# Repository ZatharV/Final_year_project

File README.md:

# Final_year_project

Industrial IoT 4.0

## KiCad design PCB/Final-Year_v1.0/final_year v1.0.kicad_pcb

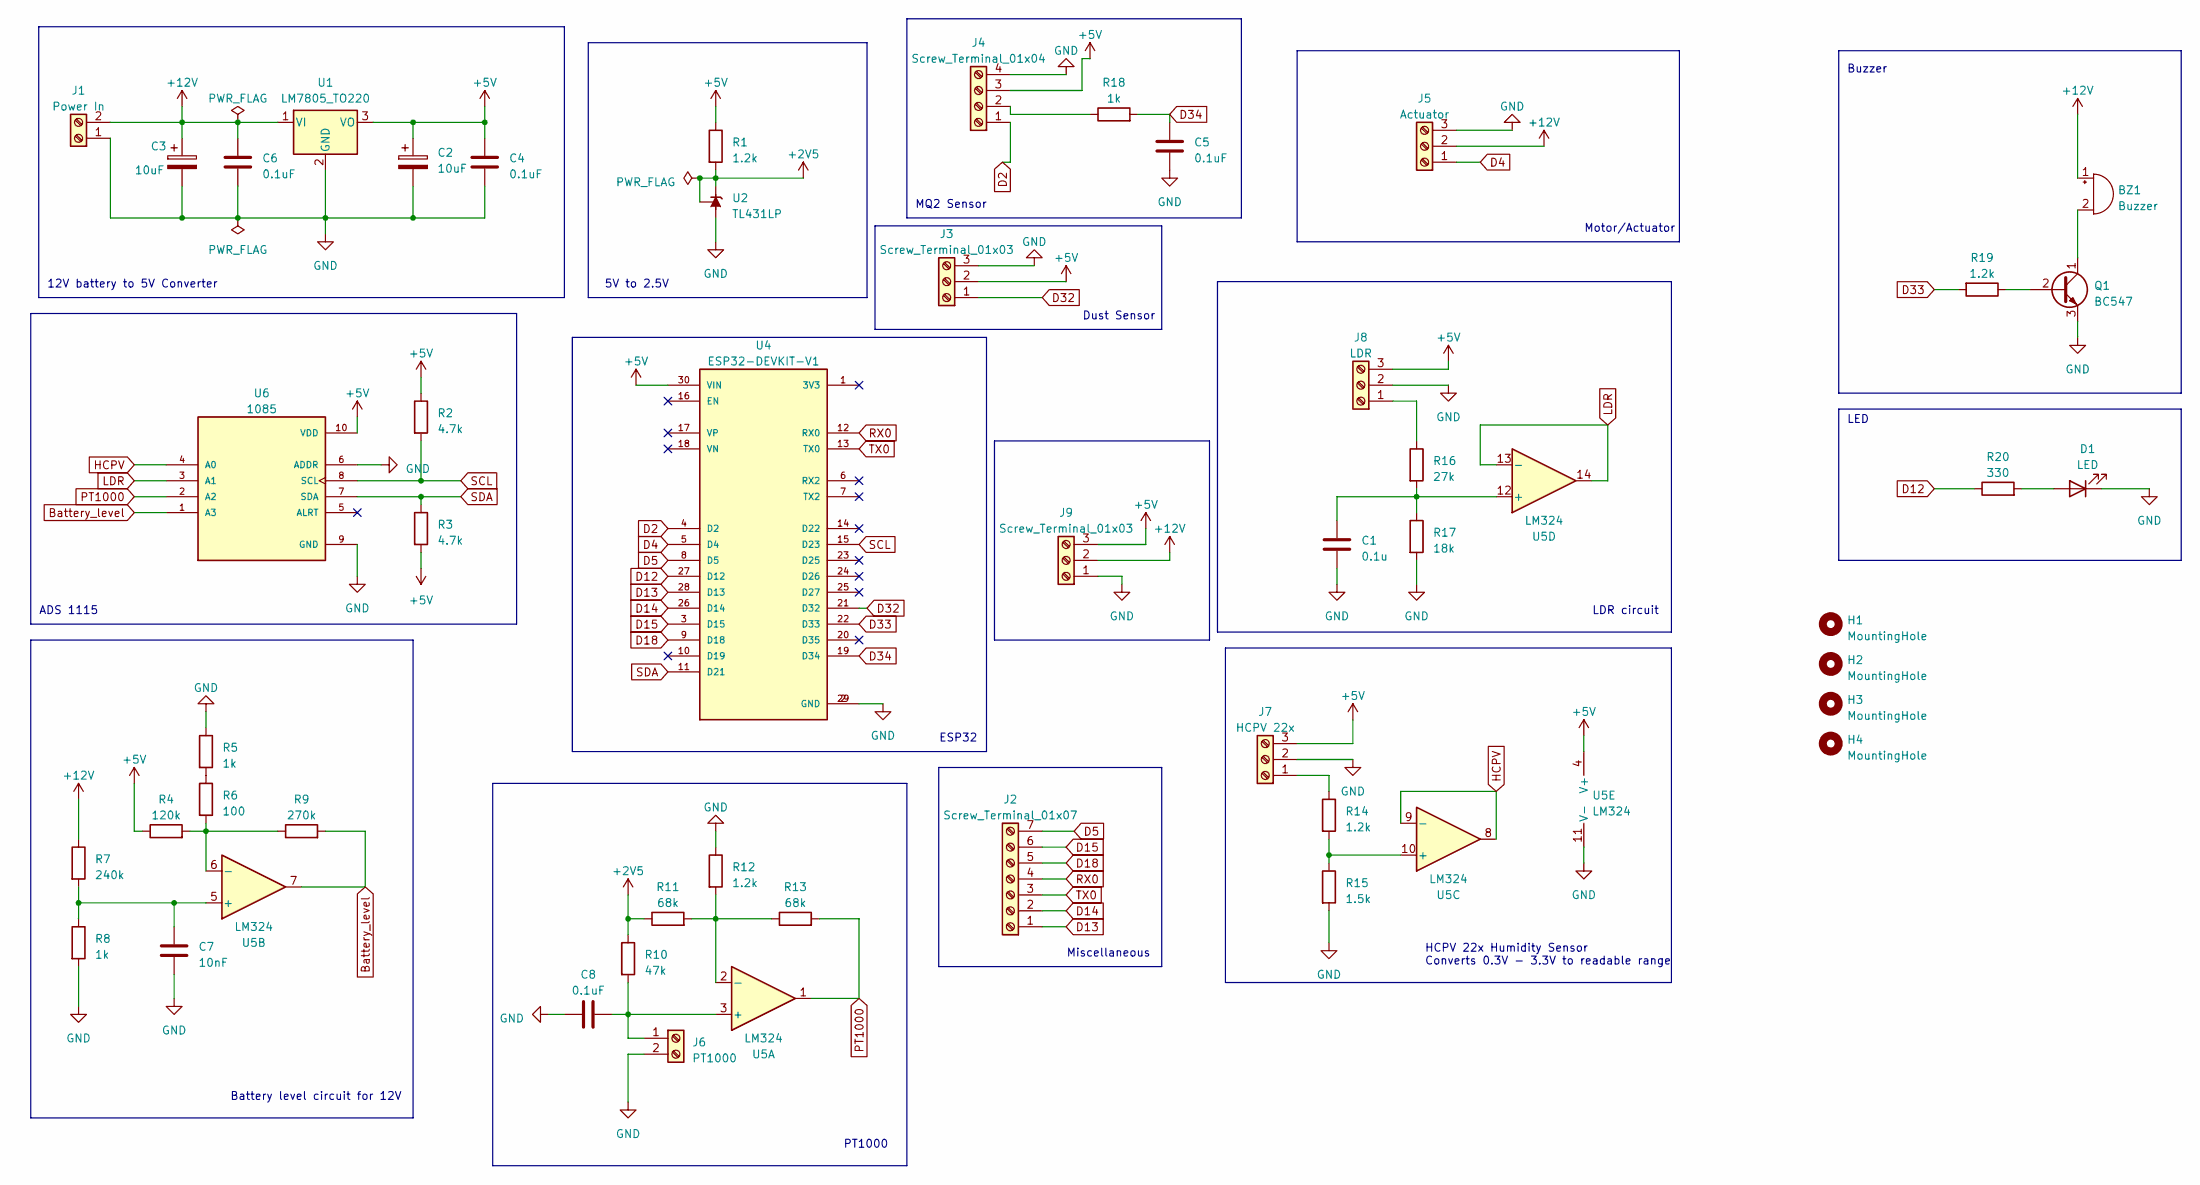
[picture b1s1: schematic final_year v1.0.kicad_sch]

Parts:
BZ1: Buzzer; Buzzer_15x7.5RM7.6
C1: 0.1u; C_Disc_D6.0mm_W2.5mm_P5.00mm
C2, C3: 10uF; CP_Radial_D4.0mm_P2.00mm
C4, C5, C6, C8: 0.1uF; C_Disc_D6.0mm_W2.5mm_P5.00mm
C7: 10nF; C_Disc_D3.8mm_W2.6mm_P2.50mm
D1: LED; LED_D5.0mm
H1, H2, H3, H4: MountingHole; MountingHole_3.2mm_M3
J1: Power In; TerminalBlock_Phoenix_MKDS-1,5-2-5.08_1x02_P5.08mm_Horizont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
J2: Screw_Terminal_01x07; TerminalBlock_Phoenix_MKDS-1,5-7-5.08_1x07_P5.08mm_Horizont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
J3, J9: Screw_Terminal_01x03; TerminalBlock_Phoenix_MKDS-1,5-3-5.08_1x03_P5.08mm_Horizont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
J4: Screw_Terminal_01x04; TerminalBlock_Phoenix_MKDS-1,5-4-5.08_1x04_P5.08mm_Horizont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
J5: Actuator; TerminalBlock_Phoenix_MKDS-1,5-3-5.08_1x03_P5.08mm_Horizont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
J6: PT1000; TerminalBlock_Phoenix_MKDS-1,5-2-5.08_1x02_P5.08mm_Horizont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
J7: HCPV 22x; TerminalBlock_Phoenix_MKDS-1,5-3-5.08_1x03_P5.08mm_Horizont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
J8: LDR; TerminalBlock_Phoenix_MKDS-1,5-3-5.08_1x03_P5.08mm_Horizont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
Q1: BC547; TO-92_Inline
R1, R12, R14, R19: 1.2k; R_Axial_DIN0207_L6.3mm_D2.5mm_P10.16mm_Horizontal
R2, R3: 4.7k; R_Axial_DIN0207_L6.3mm_D2.5mm_P10.16mm_Horizontal
R4: 120k; R_Axial_DIN0207_L6.3mm_D2.5mm_P10.16mm_Horizontal
R5, R8, R18: 1k; R_Axial_DIN0207_L6.3mm_D2.5mm_P10.16mm_Horizontal
R6: 100; R_Axial_DIN0207_L6.3mm_D2.5mm_P10.16mm_Horizontal
R7: 240k; R_Axial_DIN0207_L6.3mm_D2.5mm_P10.16mm_Horizontal
R9: 270k; R_Axial_DIN0207_L6.3mm_D2.5mm_P2.54mm_Vertical
R10: 47k; R_Axial_DIN0207_L6.3mm_D2.5mm_P10.16mm_Horizontal
R11: 68k; R_Axial_DIN0207_L6.3mm_D2.5mm_P10.16mm_Horizontal
R13: 68k; R_Axial_DIN0207_L6.3mm_D2.5mm_P2.54mm_Vertical
R15: 1.5k; R_Axial_DIN0207_L6.3mm_D2.5mm_P10.16mm_Horizontal
R16: 27k; R_Axial_DIN0207_L6.3mm_D2.5mm_P10.16mm_Horizontal
R17: 18k; R_Axial_DIN0207_L6.3mm_D2.5mm_P10.16mm_Horizontal
R20: 330; R_Axial_DIN0207_L6.3mm_D2.5mm_P10.16mm_Horizontal
U1: LM7805_TO220; TO-220-3_Vertical
U2: TL431LP; TO-92_Inline
U4: ESP32-DEVKIT-V1; MODULE_ESP32_DEVKIT_V1; PARTREV N/A
U5: LM324; DIP-14_W7.62mm
U6: 1085; ADS1115_module; PARTREV N/A

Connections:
+2V5: R1.2, R10.1, R11.1, U2.1 (REF), U2.3 (K)
+5V: C2.1, C4.1, J3.2, J4.3, J7.3, J8.3, J9.3, R1.1, R2.1, R3.2, R4.1, U1.3 (VO), U4.30 (VIN), U5.4 (V+), U6.10 (VDD)
+12V: BZ1.1 (-), C3.1, C6.1, J1.2, J5.2, J9.2, R7.1, U1.1 (VI)
Battery_level: R9.2, U5.7, U6.1 (A3)
D2: J4.1, U4.4 (D2)
D4: J5.1, U4.5 (D4)
D5: J2.7, U4.8 (D5)
D12: R20.1, U4.27 (D12)
D13: J2.1, U4.28 (D13)
D14: J2.2, U4.26 (D14)
D15: J2.6, U4.3 (D15)
D18: J2.5, U4.9 (D18)
D32: J3.1, U4.21 (D32)
D33: R19.2, U4.22 (D33)
D34: C5.1, R18.2, U4.19 (D34)
GND: C1.2, C2.2, C3.2, C4.2, C5.2, C6.2, C7.2, C8.1, D1.1 (K), J1.1, J3.3, J4.4, J5.3, J6.2, J7.2, J8.2, J9.1, Q1.3 (E), R5.1, R8.2, R12.1, R15.2, R17.2, U1.2 (GND), U2.2 (A), U4.2 (GND), U4.29 (GND), U5.11 (V-), U6.6 (ADDR), U6.9 (GND)
HCPV: U5.8, U5.9 (-), U6.4 (A0)
LDR: U5.13 (-), U5.14, U6.3 (A1)
unnamed: BZ1.2 (+), Q1.1 (C)
unnamed: D1.2 (A), R20.2
unnamed: J4.2, R18.1
unnamed: C8.2, J6.1, R10.2, U5.3 (+)
unnamed: J7.1, R14.1
unnamed: J8.1, R16.1
unnamed: Q1.2 (B), R19.1
unnamed: R5.2, R6.1
unnamed: R11.2, R12.2, R13.1, U5.2 (-)
unnamed: C7.1, R7.2, R8.1, U5.5 (+)
unnamed: R4.2, R6.2, R9.1, U5.6 (-)
unnamed: R14.2, R15.1, U5.10 (+)
unnamed: C1.1, R16.2, R17.1, U5.12 (+)
PT1000: R13.2, U5.1, U6.2 (A2)
RX0: J2.4, U4.12 (RX0)
SCL: R2.2, U4.15 (D23), U6.8 (SCL)
SDA: R3.1, U4.11 (D21), U6.7 (SDA)
TX0: J2.3, U4.13 (TX0)

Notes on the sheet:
ESP32
MQ2 Sensor
Buzzer
Miscellaneous
12V battery to 5V Converter
LED
ADS 1115
PT1000
HCPV 22x Humidity Sensor Converts 0.3V - 3.3V to readable range
Dust Sensor
Motor/Actuator
LDR circuit
Battery level circuit for 12V
5V to 2.5V

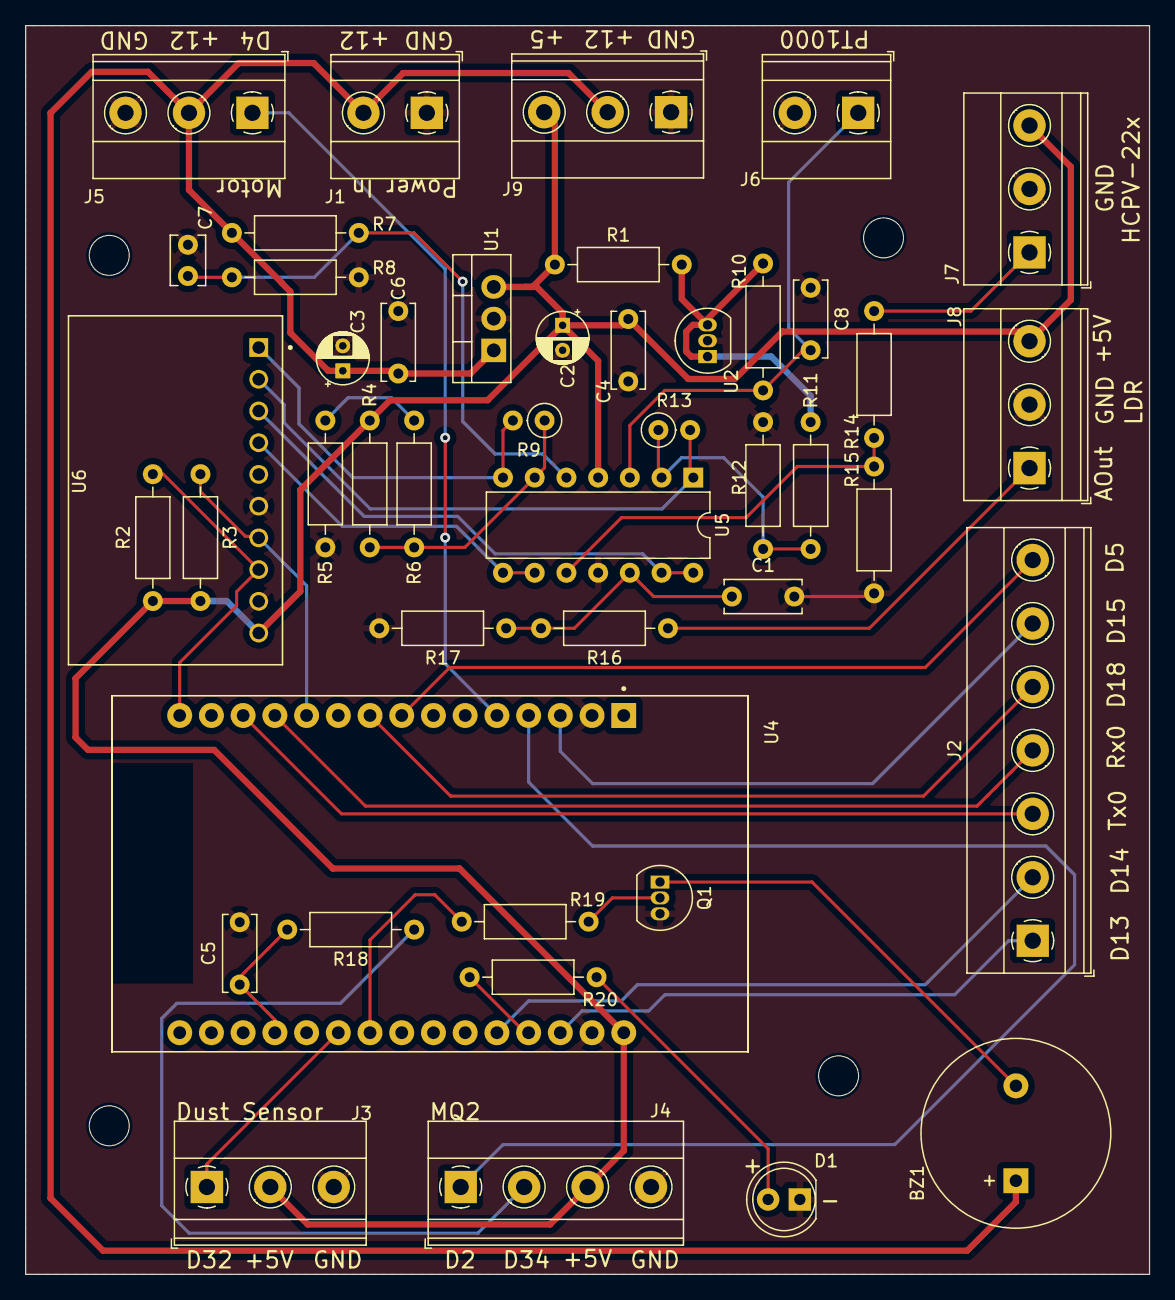
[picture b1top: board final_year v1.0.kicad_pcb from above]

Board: 2 copper layers, 90.0 x 100.0 mm, 49 parts (0 on the bottom side), 36 nets.

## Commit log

2023-02-22 Update ADC_test.ino
    changed formula for PT1000 conversion
    gives more accurate temp
2023-02-26 removed code files from from pcb branch
2023-02-26 no need of test files in pcb folder
2023-02-26 renamed
2023-02-26 removed code files in here
2023-02-26 rename
2023-02-28 Add files via upload
    Updated kicad file without any warnings
2023-02-28 no crc errors now
2023-03-03 testing
2023-03-06 added libraries
2023-03-10 address to gnd and decoupling cap to ads
2023-03-10 idf files
2023-03-11 internal adc working in success testing dust and actuator
2023-03-12 test added yo
2023-03-12 latest
2023-03-13 adding mqtt seperate
2023-03-15 new arduino files added
2023-03-15 gerber files added
2023-03-17 mqtt baseline
2023-03-30 components in process
2023-04-02 components reading sensors
2023-04-02 update2
2023-04-06 build possible with wifi error
2023-04-06 publish succesful
2023-04-07 almost done
2023-04-14 v2 done
2023-04-15 rpi new
2023-04-16 added dsm
2023-04-28 final
2023-05-01 aws s3
2023-05-01 done
2023-05-07 neww
2023-05-11 test
2023-05-17 Added Dashboard to final year main branch
2026-03-21 Bump minimatch from 3.1.2 to 3.1.5 in /dashboard/server
    Bumps [minimatch](https://github.com/isaacs/minimatch) from 3.1.2 to 3.1.5.
    - [Changelog](https://github.com/isaacs/minimatch/blob/main/changelog.md)
    - [Commits](https://github.com/isaacs/minimatch/compare/v3.1.2...v3.1.5)
    ---
    updated-dependencies:
    - dependency-name: minimatch
